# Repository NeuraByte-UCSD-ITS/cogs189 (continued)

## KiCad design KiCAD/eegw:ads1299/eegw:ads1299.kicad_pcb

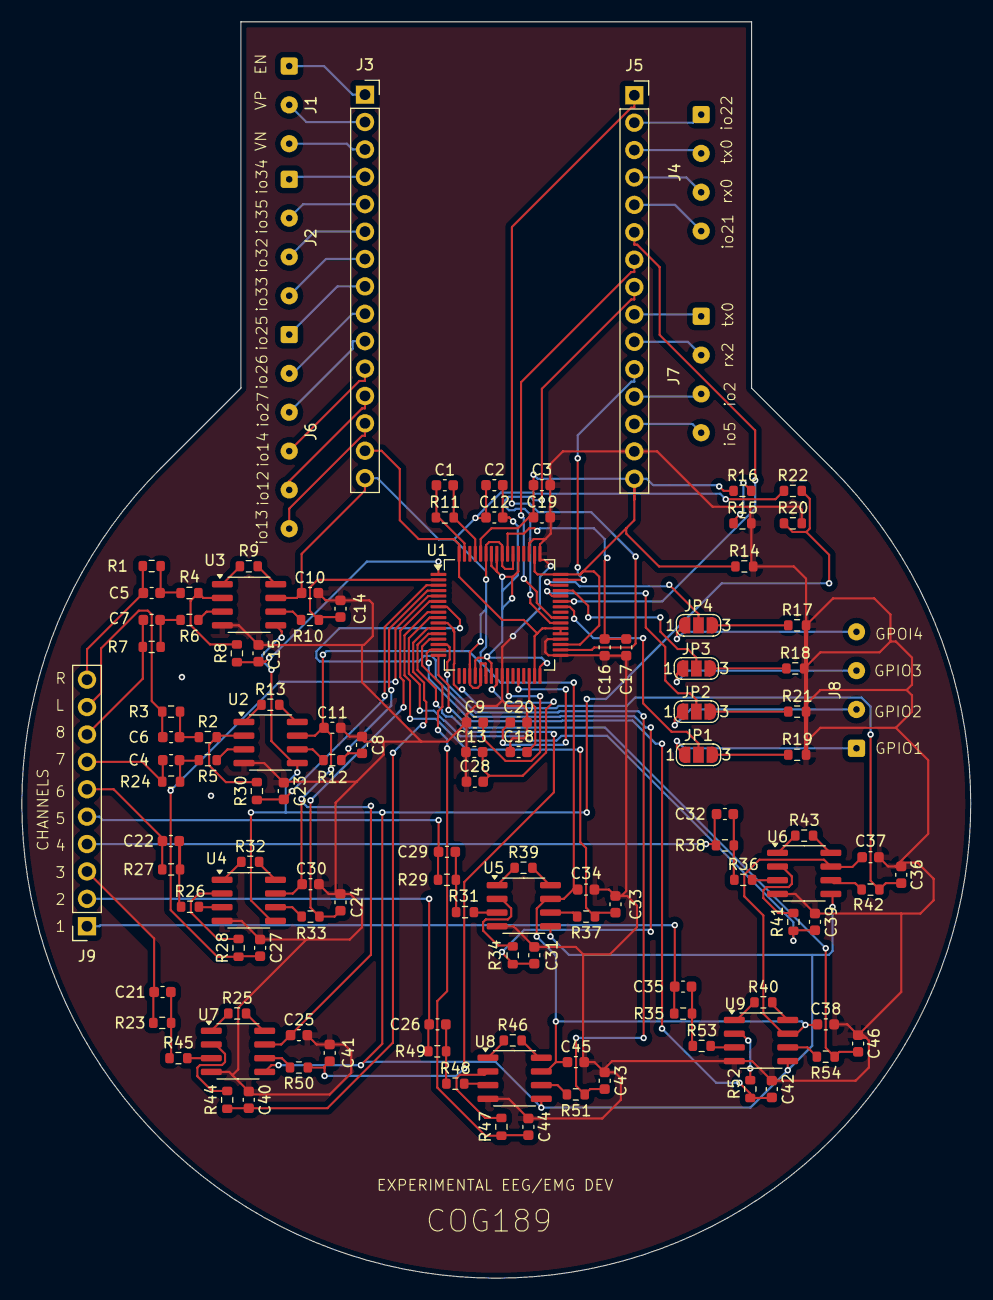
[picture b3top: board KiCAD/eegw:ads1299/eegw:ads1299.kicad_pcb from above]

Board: 2 copper layers, 88.0 x 116.5 mm, 122 parts (0 on the bottom side), 128 nets.

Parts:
C1: 1.5n; C_0603_1608Metric
C2, C3, C8, C9, C14, C15, C17, C18, C23, C24, C27, C31, C33, C36, C39, C40, C41, C42, C43, C44, C46: 1u; C_0603_1608Metric
C4, C5, C6, C7, C21, C22, C26, C29, C32, C35: 47n; C_0603_1608Metric
C10, C11, C12, C16, C19, C25, C28, C30, C34, C37, C38, C45: .1u; C_0603_1608Metric
C13: 10u; C_0603_1608Metric
C20: 100u; C_0603_1608Metric
J1: ESP32-L; SolderWire-0.1sqmm_1x03_P3.6mm_D0.4mm_OD1mm
J2: ESP32-L3; SolderWire-0.1sqmm_1x04_P3.6mm_D0.4mm_OD1mm
J3: ESP32_Left; PinSocket_1x15_P2.54mm_Vertical
J4: ESP32-R; SolderWire-0.1sqmm_1x04_P3.6mm_D0.4mm_OD1mm
J5: ESP32_Right; PinSocket_1x15_P2.54mm_Vertical
J6: ESP32-L2; SolderWire-0.1sqmm_1x06_P3.6mm_D0.4mm_OD1mm
J7: ESP32-R2; SolderWire-0.1sqmm_1x04_P3.6mm_D0.4mm_OD1mm
J8: gpioADS; SolderWire-0.1sqmm_1x04_P3.6mm_D0.4mm_OD1mm
J9: Conn_01x10; PinSocket_1x10_P2.54mm_Vertical
JP1, JP2, JP3, JP4: SJ_3_Opn; SolderJumper-3_P1.3mm_Open_RoundedPad1.0x1.5mm_NumberLabels
R1, R3, R7, R23, R24, R27, R29, R35, R38, R49: 51k; R_0603_1608Metric
R2, R4, R5, R6, R9, R13, R14, R15, R16, R17, R18, R19, R20, R21, R22, R25, R26, R31, R32, R36, R39, R40, R43, R45, R46, R48, R53: 10k; R_0603_1608Metric
R8, R10, R12, R30: 630; R_0603_1608Metric
R11: 1M; R_0603_1608Metric
R28, R33, R34, R37, R41, R42, R44, R47, R50, R51, R52, R54: 1.5k; R_0603_1608Metric
U1: ADS1299IPAG; TQFP-64_10x10mm_P0.5mm
U2, U3, U4, U5, U6, U7, U8, U9: INA128U; SOIC-8_3.9x4.9mm_P1.27mm

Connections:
+1V65: R15.1, R16.2
+2V5: R20.1, R22.2, U2.5 (Ref), U3.5 (Ref), U4.5 (Ref), U5.5 (Ref), U6.5 (Ref), U7.5 (Ref), U8.5 (Ref), U9.5 (Ref)
+3V3: C3.1, C19.1, J5.15, R14.1, R16.1, U1.35 (~PWDN), U1.48 (DVDD), U1.50 (DVDD), U1.60 (RLDREF)
+5V: C2.1, C10.1, C11.1, C12.1, C25.1, C30.1, C34.1, C37.1, C38.1, C45.1, J3.15, R22.1, U1.19 (AVDD), U1.21 (AVDD), U1.22 (AVDD), U1.54 (AVDD1), U1.56 (AVDD), U1.59 (AVDD), U2.7 (V+), U3.7 (V+), U4.7 (V+), U5.7 (V+), U6.7 (V+), U7.7 (V+), U8.7 (V+), U9.7 (V+)
CS: J5.8, U1.39 (~CS)
DRDY: J5.11, U1.47 (~DRDY)
GND: C3.2, C8.2, C9.1, C10.2, C11.2, C13.1, C14.2, C15.2, C16.1, C17.1, C18.1, C19.2, C20.2, C23.2, C24.2, C25.2, C27.2, C28.1, C30.2, C31.2, C33.2, C34.2, C36.2, C37.2, C38.2, C39.2, C40.2, C41.2, C42.2, C43.2, C44.2, C45.2, C46.2, J5.14, R14.2, R15.2, R17.2, R18.2, R19.2, R20.2, R21.2, U1.25 (VREFN), U1.33 (DGND), U1.36 (~RESET), U1.49 (DGND), U1.51 (DGND), U2.4 (V-), U3.4 (V-), U4.4 (V-), U5.4 (V-), U6.4 (V-), U7.4 (V-), U8.4 (V-), U9.4 (V-)
GNDA: C2.2, C12.2, U1.20 (AVSS), U1.23 (AVSS), U1.32 (AVSS), U1.53 (AVSS1), U1.57 (AVSS), U1.58 (AVSS)
MISO: J5.6, U1.43 (DOUT)
MOSI: J5.1, U1.34 (DIN)
unnamed: C26.2, R48.1, R49.2
unnamed: C21.2, R23.2, R45.1
unnamed: C32.2, R36.1, R38.2
unnamed: C29.2, R29.2, R31.1
unnamed: C22.2, R26.1, R27.2
unnamed: C35.2, R35.2, R53.1
unnamed: C6.2, R2.1, R3.2
unnamed: C4.2, R5.1, R24.2
unnamed: C5.2, R1.2, R4.1
unnamed: C7.2, R6.1, R7.2
unnamed: JP4.3 (B), R17.1
unnamed: JP3.3 (B), R18.1
unnamed: JP2.3 (B), R21.1
unnamed: JP1.3 (B), R19.1
unnamed: R40.1, U9.1 (Rg)
unnamed: R40.2, U9.8 (Rg)
unnamed: R54.1, U9.6
unnamed: R46.1, U8.1 (Rg)
unnamed: R46.2, U8.8 (Rg)
unnamed: R51.1, U8.6
unnamed: R25.1, U7.1 (Rg)
unnamed: R25.2, U7.8 (Rg)
unnamed: R50.1, U7.6
unnamed: R43.1, U6.1 (Rg)
unnamed: R43.2, U6.8 (Rg)
unnamed: R42.1, U6.6
unnamed: R39.1, U5.1 (Rg)
unnamed: R39.2, U5.8 (Rg)
unnamed: R37.1, U5.6
unnamed: R32.1, U4.1 (Rg)
unnamed: R32.2, U4.8 (Rg)
unnamed: R33.1, U4.6
unnamed: R13.1, U2.1 (Rg)
unnamed: R13.2, U2.8 (Rg)
unnamed: R12.1, U2.6
unnamed: R9.1, U3.1 (Rg)
unnamed: R9.2, U3.8 (Rg)
unnamed: R10.1, U3.6
unnamed: C1.2, R11.2, U1.61 (RLDINV)
unnamed: C1.1, R11.1, U1.63 (RLDOUT)
unnamed: C20.1, U1.28 (VCAP1)
unnamed: C18.2, U1.30 (VCAP2)
unnamed: C16.2, C17.2, U1.55 (VCAP3)
unnamed: C9.2, U1.26 (VCAP4)
unnamed: C13.2, C28.2, U1.24 (VREFP)
unnamed: R48.2, U8.3 (+)
unnamed: R47.1, U8.2 (-)
unnamed: R53.2, U9.3 (+)
unnamed: R52.1, U9.2 (-)
unnamed: R45.2, U7.3 (+)
unnamed: R44.1, U7.2 (-)
unnamed: R36.2, U6.3 (+)
unnamed: R41.1, U6.2 (-)
unnamed: R31.2, U5.3 (+)
unnamed: R34.1, U5.2 (-)
unnamed: R26.2, U4.3 (+)
unnamed: R28.1, U4.2 (-)
unnamed: R5.2, U2.3 (+)
unnamed: R2.2, R30.1, U2.2 (-)
unnamed: R6.2, U3.3 (+)
unnamed: R4.2, R8.1, U3.2 (-)
SCLK: J5.7, U1.40 (SCLK)
electrode_1: C35.1, J9.1, R35.1
electrode_2: C26.1, J9.2, R49.1
electrode_3: C21.1, J9.3, R23.1
electrode_4: C32.1, J9.4, R38.1
electrode_5: C29.1, J9.5, R29.1
electrode_6: C22.1, J9.6, R27.1
electrode_7: C4.1, J9.7, R24.1
electrode_8: C7.1, J9.8, R7.1
en: J1.1, J3.1
gnd: J3.14, U1.31 (RESV1), U1.37 (CLK), U1.38 (START), U1.64 (WCT)
gpio1ADS: J8.1, JP1.1 (A)
gpio2ADS: J8.2, JP2.1 (A)
gpio3ADS: J8.3, JP3.1 (A)
gpio4ADS: J8.4, JP4.1 (A)
in1n: C42.1, R52.2, U1.15 (IN1N)
in1p: C46.1, R54.2, U1.16 (IN1P)
in2n: C44.1, R47.2, U1.13 (IN2N)
in2p: C43.1, R51.2, U1.14 (IN2P)
in3n: C40.1, R44.2, U1.11 (IN3N)
in3p: C41.1, R50.2, U1.12 (IN3P)
in4n: C39.1, R41.2, U1.9 (IN4N)
in4p: C36.1, R42.2, U1.10 (IN4P)
in5n: C31.1, R34.2, U1.7 (IN5N)
in5p: C33.1, R37.2, U1.8 (IN5P)
in6n: C27.1, R28.2, U1.5 (IN6N)
in6p: C24.1, R33.2, U1.6 (IN6P)
in7n: C23.1, R30.2, U1.3 (IN7P)
in7p: C8.1, R12.2, U1.4 (IN7N)
in8n: C15.1, R8.2, U1.1 (IN8N)
in8p: C14.1, R10.2, U1.2 (IN8P)
io2: J5.12, J7.3
io12: J3.12, J6.5
io13: J3.13, J6.6
io14: J3.11, J6.4
io15: J5.13, J7.4
io21: J4.4, J5.5
io22: J4.1, J5.2
io25: J3.8, J6.1
io26: J3.9, J6.2
io27: J3.10, J6.3
io32: J2.3, J3.6
io33: J2.4, J3.7
io34: J2.1, J3.4
io35: J2.2, J3.5
pin1: JP1.2 (C), U1.42 (GPIO1)
pin2: JP2.2 (C), U1.44 (GPIO2)
pin3: JP3.2 (C), U1.45 (GPIO3)
pin4: JP4.2 (C), U1.46 (GPIO4)
ref_electrodeL: C6.1, J9.9, R3.1
ref_electrodeR: C5.1, J9.10, R1.1
rx0: J4.3, J5.4
rx2: J5.10, J7.2
tx0: J4.2, J5.3
tx2: J5.9, J7.1
vn: J1.3, J3.3
vp: J1.2, J3.2

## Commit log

2025-02-12 Update README.md
    Adding all team information
2025-02-12 Update README.md
    added correct git clone url
2025-02-13 Update README.md
    updating GitHub usernames to table
2025-02-13 added KiCAD and hardware pictures
2025-02-13 updated kicad renumbered
2025-02-13 organized hardware files & included hardware documentation guide
2025-02-13 updating README for latest changes
2025-02-16 added new kicad and pics
2025-02-16 update filled zone & geograpgically annotated pcb
2025-02-16 added pictures and renamed it
2025-02-17 fixed zone fills for GNDA/GNDD/GND &added grb file
2025-02-18 pyautogui demo
2025-02-18 forgot something...
2025-02-19 simulating mapping
2025-02-20 Added OpenVEP and dependencies
2025-02-21 removed OpenVEP
2025-02-21 simulating_mapping
2025-02-21 adding openvep
2025-02-21 configuring Git LFS for large binary files
2025-02-21 Track all large file extensions with LFS
2025-02-21 Ignore .DS_Store
2025-02-21 Simon's Notes on OpenVEP
2025-02-22 Updated OpenVEP code with 4 classes (in progress)
2025-02-23 Finished with the GUI aspect of OpenVEP
2025-02-24 deleted Brainda and Pyenv
2025-02-25 Updated train_trca
2025-02-26 adjusted folder name and stimulus class in training for 4 class
2025-02-28 Added Data recorded from lab and model file
2025-02-28 completed SSVEP without cursor mapping
2025-02-28 Track large MOV and JPEG files with Git LFS
2025-02-28 adding video and image
2025-02-28 embedding video
2025-02-28 adding video
2025-02-28 Added Brainda Folder
2025-02-28 Updated Readme with setup steps
2025-02-28 Added Brainda Repo
2025-03-03 Updated the README
2025-03-05 Mapped cursor to predicted commands
2025-03-05 Updated README with setup instructions
2025-03-05 Updated Lab Computer Setup instructions
2025-03-05 Added data file explanation section
2025-03-05 Fixed repo formatting
2025-03-10 preserved successful ssvep trial and separated ongoing experimental mapping
2025-03-11 gitignore update
2025-03-11 deleting stuff
2025-03-12 added KiCAD folder & unfinished Hardware code
2025-03-14 Add vis file
2025-03-14 Added VEP data
2025-03-16 visualizations & experiment simulations (without cursor mapping)
2025-03-16 naming
2025-03-16 brainda installation
2025-03-17 Added cursor mapping to simulation
2025-03-18 updated simulation
